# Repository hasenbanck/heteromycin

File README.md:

# Heteromycin - 3D printer board

Heteromycin is a 3D printer controller that aims to provide a full stack user
experience around Octoprint / Marlin using a custom designed board that
integrates a Raspberry Pi 3 or Zero W. It will also provide a solid, powerfull
hardware by utilizing quality components, a STM32 32bit MCU and powerfull
TMC5160 or TMC2160 driver (SD / SPI mode).

## Features

* 32bit STM32H743VI 400Mhz / 1024KiB RAM / 2MiB Flash MCU / 4 KiB EEPROM
* Integrated Raspberry Pi 3 / Zero W HAT connector as the main user interface
* Integrated DC/DC switching module for 5V / 3.3V power supply
* 5x TMC5160 or TMC2160 stepper driver with 8x external Power MOSFET each
* 3x high power MOSFET for heating (2x heater, 1x heatbed, 24V)
* 4x low power MOSFET for fans (5V or 24V)
* 40 pin external connector for STM32 and Pi GPIO pins
  * GPIO
  * PWM
  * UART
  * SPI
  * I2C
  * 3.3V / 5V / GND for external power consumption
* Micro SD Card for storing GCODE files (directa MCU access)
* Designed for a 24V power supply
* Automotive fuses
* Quality connectors
* Octoprint plugin for flashing the firmware of the board (STM32)

## Roadmap

* Hardware
  * [x] Describe the general functionality and select the main components
  * [x] Draw the schematics of the PCB
  * [x] Placement & routing of the PCB
  * [ ] Production of a development board
  * [ ] Testing the PCB
  * [ ] Repreat until hardware is finished
* Software
  * [x] Write arduino core board definition once first PCB design is finished
  * [ ] Write PIN file for Marlin
  * [ ] Test board (esp. the TMC*160 driver)
  * [ ] Octoprint plugin for firmware upgrade
  * [ ] STM32flash rewrite (fix I2C and add SPI, maybe rewrite in rust)
  * [ ] Create a script / image with Octoprint with the plugin / tools
  preinstalled
  * [ ] Documentation

## Alternative Parts

### Stepper driver

You can use both TMC5160 or TMC2160 as the stepper driver, since they both are
functionally / pin equal when used in SD / SPI-Mode.

It doesn't mater choosing one over the other, other than price and availability.

Fine tuning of the MOSFET driver may be necessary.

## License

The hardware is licensed under CERN OHL version 1.2.
The software is licensed under GNU GPL v3.

The files under PCB/packages3d are excluded from this license and are provided
under fair use terms for this open-source project.

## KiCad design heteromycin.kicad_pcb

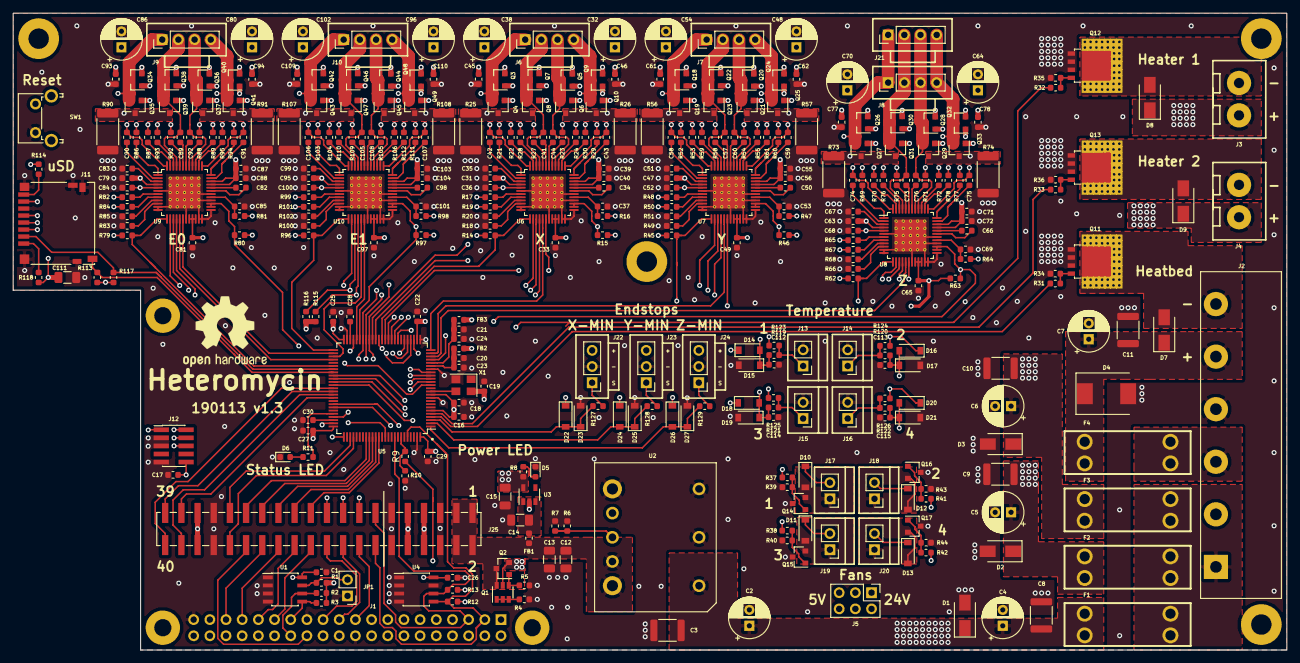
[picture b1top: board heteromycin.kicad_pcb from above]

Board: 4 copper layers, 200.0 x 100.0 mm, 373 parts (1 on the bottom side), 293 nets.

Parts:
C1, C16, C17, C18, C19, C22, C23, C24, C25, C26, C27, C29, C31, C33, C39, C40, C47, C49, C55, C56, C63, C65, C71, C72, C79, C81, C87, C88, C95, C97, C103, C104, C112, C113, C114, C115: 100nF; C_0603_1608Metric
C2, C4, C5, C6, C7, C32, C38, C48, C54, C64, C70, C80, C86, C96, C102: 100uF; CP_Radial_D6.3mm_P2.50mm
C3, C8, C9, C10, C11: 100nF; C_1812_4532Metric
C12, C14: 22uF; C_1206_3216Metric
C13: 100nF; C_1206_3216Metric
C15, C111: 10uF; C_1206_3216Metric
C20, C21: 1uF; C_0603_1608Metric
C28, C30, C35, C36, C51, C52, C67, C68, C83, C84, C99, C100: 2.2uF; C_0603_1608Metric
C34, C50, C66, C82, C98: 22nF; C_0603_1608Metric
C37, C45, C46, C53, C61, C62, C69, C77, C78, C85, C93, C94, C101, C109, C110: 470nF; C_0603_1608Metric
C41, C42, C43, C44, C57, C58, C59, C60, C73, C74, C75, C76, C89, C90, C91, C92, C105, C106, C107, C108: 220nF; C_0603_1608Metric
D1, D2, D3: SMAJ28A; D_SMA
D4: S3A-13-F; D_SMC
D5: LTST-C194KGKT; LED_0603_1608Metric
D6: LTST-C194KSKT; LED_0603_1608Metric
D7, D8, D9: SK310A-LTP; D_SMA
D10, D11, D12, D13, D14, D15, D16, D17, D18, D19, D20, D21, D22, D23, D24, D25, D26, D27: BAT54GWJ; D_SOD-123
F1, F2, F3, F4: 3557-2; KEYSTONE-FUSE-3557-2
FB1, FB2, FB3: MPZ1608S221A; R_0603_1608Metric
H1, H2, H5: MountingHole_2.7mm_M2.5_Pad
H3, H4, H6, H7: MountingHole_3.2mm_M3_Pad
J1: M20-7832046; PinSocket_2x20_P2.54mm_Vertical
J2: 4DB-P108-06
J3, J4: 39531-1002
J5: Conn_02x03_Counter_Clockwise; PinHeader_2x03_P2.54mm_Vertical
J6, J7, J8, J9, J10, J21: 70543-0003
J11: DM3D-SF; microSD_HC_Hirose_DM3D-SF
J12: 20021121-00010C4LF; PinHeader_2x05_P1.27mm_Vertical_SMD
J13, J14, J15, J16, J17, J18, J19, J20: 70543-0001
J22, J23, J24: 70543-0002
J25: Conn_02x20_Odd_Even; PinHeader_2x20_P2.54mm_Vertical_SMD
JP1: Jumper_2_Open; PinHeader_1x02_P2.54mm_Vertical
LOGO1: Logo_Open_Hardware_Large; OSHW-Logo2_14.6x12mm_SilkScreen
Q1: DMMT5401; SOT-23-6
Q2: DMG2305UX; SOT-23
Q3, Q4, Q5, Q6, Q7, Q8, Q9, Q10, Q14, Q15, Q16, Q17, Q18, Q19, Q20, Q21, Q22, Q23, Q24, Q25, Q26, Q27, Q28, Q29, Q30, Q31, Q32, Q33, Q34, Q35, Q36, Q37, Q38, Q39, Q40, Q41, Q42, Q43, Q44, Q45, Q46, Q47, Q48, Q49: IRLML0030TRPbF; SOT-23
Q11, Q12, Q13: PSMN1R2-30YLC,115; SOT-669_LFPAK_ThermalVias-1
R1, R5, R14, R15, R45, R46, R62, R63, R79, R80, R96, R97, R113, R114, R115, R116, R117, R118: 47k; R_0603_1608Metric
R2, R3: 3.9K; R_0603_1608Metric
R4, R9: 10k; R_0603_1608Metric
R6: 20k; R_0603_1608Metric
R7: 15k; R_0603_1608Metric
R8, R11, R127, R128, R129: 1k; R_0603_1608Metric
R10, R34, R35, R36, R39, R40, R43, R44: 100k; R_0603_1608Metric
R12, R13, R119, R120, R121, R122, R123, R124, R125, R126: 4.7k; R_0603_1608Metric
R16, R47, R64, R81, R98: 2.2; R_0603_1608Metric
R17, R18, R19, R20, R48, R49, R50, R51, R65, R66, R67, R68, R82, R83, R84, R85, R99, R100, R101, R102: 47; R_0603_1608Metric
R21, R22, R23, R24, R27, R28, R29, R30, R52, R53, R54, R55, R58, R59, R60, R61, R69, R70, R71, R72, R75, R76, R77, R78, R86, R87, R88, R89, R92, R93, R94, R95, R103, R104, R105, R106, R109, R110, R111, R112: 10; R_0603_1608Metric
R25, R26, R56, R57, R73, R74, R90, R91, R107, R108: 0.1; R_2512_6332Metric
R31, R32, R33, R37, R38, R41, R42: 100; R_0603_1608Metric
SW1: PTS645VL39-2; SW_Tactile_SPST_Angled_PTS645Vx39-2LFS
U1, U4: CAT24C32; SOIC-8_3.9x4.9mm_P1.27mm
U2: i3A
U3: AP7365-33WG-7; SOT-23-5
U5: STM32H743VI; TQFP-100_14x14mm_P0.5mm
U6, U7, U8, U9, U10: TMC2160-TA; TQFP-48-1EP_7x7mm_P0.5mm_EP5x5mm_ThermalVias
X1: ECS-TXO-3225-250-TR; ECS-TXO-3225

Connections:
/Connectors/MCU_MISO: J11.7, J25.17, R115.1, U5.43, U6.16, U7.16, U8.16, U9.16, U10.16
/Connectors/MCU_MOSI: J11.3, J25.19, R116.1, U5.44, U6.15, U7.15, U8.15, U9.15, U10.15
/Connectors/MCU_SCK: J11.5, J25.15, U5.42, U6.14, U7.14, U8.14, U9.14, U10.14
/Connectors/PI_SCK: J1.23, J25.20, U5.29
/Connectors/PI_SS1: J1.26, J25.30
/Connectors/PWM_EXT1: J25.37, U5.66
/Connectors/PWM_EXT2: J25.38, U5.65
/Connectors/PWM_EXT3: J25.39, U5.64
/Connectors/PWM_EXT4: J25.40, U5.63
/Connectors/RX: J25.32, U5.79
/Connectors/SCL: J1.5, J25.13, R13.1, U4.6, U5.92
/Connectors/SDA: J1.3, J25.14, R12.1, U4.5, U5.96
/Connectors/SWCLK: J12.4, U5.76
/Connectors/SWDIO: J12.2, U5.72
/Connectors/SWO: J12.6, U5.89
/Connectors/TEMP1: C112.1, D14.2, D15.1, R119.2, U5.18
/Connectors/TEMP2: C113.1, D16.2, D17.1, R120.2, U5.17
/Connectors/TEMP3: C114.1, D18.2, D19.1, R121.2, U5.16
/Connectors/TEMP4: C115.1, D20.2, D21.1, R122.2, U5.15
/Connectors/TX: J25.31, U5.78
/Connectors/X_MIN: D22.2, D23.1, R127.2, U5.3
/Connectors/Y_MIN: D24.2, D25.1, R128.2, U5.2
/Connectors/Z_MIN: D26.2, D27.1, R129.2, U5.1
/Connectors/nRESET: C17.2, J1.12, J12.10, SW1.2, U5.14
/MCU/BOOT: J1.7, R9.1
/MCU/BOOTpin: R9.2, R10.2, U5.94
/MCU/CLK: U5.12, X1.3
/MCU/D1: J25.21, U5.87
/MCU/D2: J25.23, U5.86
/MCU/D3: J25.25, U5.85
/MCU/D4: J25.27, U5.84
/MCU/D5: J25.29, U5.83
/MCU/MCU_SS: J1.24, U5.28
/MCU/PWM_BED: R31.2, U5.4
/MCU/PWM_FAN1: R37.2, U5.59
/MCU/PWM_FAN2: R41.2, U5.60
/MCU/PWM_FAN3: R38.2, U5.61
/MCU/PWM_FAN4: R42.2, U5.62
/MCU/PWM_HEAT1: R32.2, U5.22
/MCU/PWM_HEAT2: R33.2, U5.5
/MCU/SD_DETECT: J11.10, R113.1, U5.58
/MCU/STATUS_LED: R11.1, U5.71
/MCU/VCAP1: C28.2, U5.48
/MCU/VCAP2: C30.2, U5.73
/MCU/VDDA: C21.1, C24.1, FB3.1, U5.21
/MCU/VREF+: C20.2, C23.2, FB2.1, U5.20
/Raspberry Pi Connector/D1: J1.29, J25.22
/Raspberry Pi Connector/D2: J1.31, J25.24
/Raspberry Pi Connector/D3: J1.33, J25.26
/Raspberry Pi Connector/D4: J1.35, J25.28
/Raspberry Pi Connector/ID_SC_EEPROM: J1.28, R2.2, U1.6
/Raspberry Pi Connector/ID_SD_EEPROM: J1.27, R3.2, U1.5
/Raspberry Pi Connector/MISO: J1.21, J25.18, U5.30
/Raspberry Pi Connector/MOSI: J1.19, J25.16, U5.31
/Raspberry Pi Connector/RX: J1.10, U5.68
/Raspberry Pi Connector/TX: J1.8, U5.69
/Raspberry Pi Connector/VDD5V_HAT: J1.2, J1.4, Q1.5, Q2.2
/SD Card Reader/SS: J11.2, R117.1, U5.57
/Steper Motor Y/5VOUT: C52.1, R47.2, U7.5
/Steper Motor Y/12VOUT: C51.1, U7.3
/Steper Motor Y/BMA1: C60.2, J7.3, Q20.3, Q21.2, U7.40
/Steper Motor Y/BMA2: C59.2, J7.4, Q24.3, Q25.2, U7.37
/Steper Motor Y/BMB1: C58.2, J7.1, Q18.3, Q19.2, U7.48
/Steper Motor Y/BMB2: C57.2, J7.2, Q22.3, Q23.2, U7.45
/Steper Motor Y/CA1: C60.1, U7.42
/Steper Motor Y/CA2: C59.1, U7.35
/Steper Motor Y/CB1: C58.1, U7.2
/Steper Motor Y/CB2: C57.1, U7.43
/Steper Motor Y/CPI: C50.1, U7.32
/Steper Motor Y/CPO: C50.2, U7.31
/Steper Motor Y/DIAG: R46.1, U5.40, U7.26, U7.27
/Steper Motor Y/DIR: U5.35, U7.18
/Steper Motor Y/HA1: R54.1, U7.41
/Steper Motor Y/HA2: R60.2, U7.36
/Steper Motor Y/HB1: R52.1, U7.1
/Steper Motor Y/HB2: R58.2, U7.44
/Steper Motor Y/LA1: R55.1, U7.39
/Steper Motor Y/LA2: R61.2, U7.38
/Steper Motor Y/LB1: R53.1, U7.47
/Steper Motor Y/LB2: R59.2, U7.46
/Steper Motor Y/SRAH: R50.1, U7.8
/Steper Motor Y/SRAL: R51.1, U7.9
/Steper Motor Y/SRBH: R48.2, U7.7
/Steper Motor Y/SRBL: R49.1, U7.10
/Steper Motor Y/SS: R45.1, U5.36, U7.13
/Steper Motor Y/STEP: U5.24, U7.17
/Steper Motor Y/VCC: C53.1, R47.1, U7.29
/Stepper Motor E0/5VOUT: C84.1, R81.2, U9.5
/Stepper Motor E0/12VOUT: C83.1, U9.3
/Stepper Motor E0/BMA1: C92.2, J9.3, Q36.3, Q37.2, U9.40
/Stepper Motor E0/BMA2: C91.2, J9.4, Q40.3, Q41.2, U9.37
/Stepper Motor E0/BMB1: C90.2, J9.1, Q34.3, Q35.2, U9.48
/Stepper Motor E0/BMB2: C89.2, J9.2, Q38.3, Q39.2, U9.45
/Stepper Motor E0/CA1: C92.1, U9.42
/Stepper Motor E0/CA2: C91.1, U9.35
/Stepper Motor E0/CB1: C90.1, U9.2
/Stepper Motor E0/CB2: C89.1, U9.43
/Stepper Motor E0/CPI: C82.1, U9.32
/Stepper Motor E0/CPO: C82.2, U9.31
/Stepper Motor E0/DIAG: R80.1, U5.47, U9.26, U9.27
/Stepper Motor E0/DIR: U5.52, U9.18
/Stepper Motor E0/HA1: R88.1, U9.41
/Stepper Motor E0/HA2: R94.2, U9.36
/Stepper Motor E0/HB1: R86.1, U9.1
/Stepper Motor E0/HB2: R92.2, U9.44
/Stepper Motor E0/LA1: R89.1, U9.39
/Stepper Motor E0/LA2: R95.2, U9.38
/Stepper Motor E0/LB1: R87.1, U9.47
/Stepper Motor E0/LB2: R93.2, U9.46
/Stepper Motor E0/SRAH: R84.1, U9.8
/Stepper Motor E0/SRAL: R85.1, U9.9
/Stepper Motor E0/SRBH: R82.2, U9.7
/Stepper Motor E0/SRBL: R83.1, U9.10
/Stepper Motor E0/SS: R79.1, U5.56, U9.13
/Stepper Motor E0/STEP: U5.54, U9.17
/Stepper Motor E0/VCC: C85.1, R81.1, U9.29
/Stepper Motor E1/5VOUT: C100.1, R98.2, U10.5
/Stepper Motor E1/12VOUT: C99.1, U10.3
/Stepper Motor E1/BMA1: C108.2, J10.3, Q44.3, Q45.2, U10.40
/Stepper Motor E1/BMA2: C107.2, J10.4, Q48.3, Q49.2, U10.37
/Stepper Motor E1/BMB1: C106.2, J10.1, Q42.3, Q43.2, U10.48
/Stepper Motor E1/BMB2: C105.2, J10.2, Q46.3, Q47.2, U10.45
/Stepper Motor E1/CA1: C108.1, U10.42
/Stepper Motor E1/CA2: C107.1, U10.35
/Stepper Motor E1/CB1: C106.1, U10.2
/Stepper Motor E1/CB2: C105.1, U10.43
/Stepper Motor E1/CPI: C98.1, U10.32
/Stepper Motor E1/CPO: C98.2, U10.31
/Stepper Motor E1/DIAG: R97.1, U5.45, U10.26, U10.27
/Stepper Motor E1/DIR: U5.46, U10.18
/Stepper Motor E1/HA1: R105.1, U10.41
/Stepper Motor E1/HA2: R111.2, U10.36
/Stepper Motor E1/HB1: R103.1, U10.1
/Stepper Motor E1/HB2: R109.2, U10.44
/Stepper Motor E1/LA1: R106.1, U10.39
/Stepper Motor E1/LA2: R112.2, U10.38
/Stepper Motor E1/LB1: R104.1, U10.47
/Stepper Motor E1/LB2: R110.2, U10.46
/Stepper Motor E1/SRAH: R101.1, U10.8
/Stepper Motor E1/SRAL: R102.1, U10.9
/Stepper Motor E1/SRBH: R99.2, U10.7
/Stepper Motor E1/SRBL: R100.1, U10.10
/Stepper Motor E1/SS: R96.1, U5.51, U10.13
/Stepper Motor E1/STEP: U5.53, U10.17
/Stepper Motor E1/VCC: C101.1, R98.1, U10.29
/Stepper Motor X/5VOUT: C36.1, R16.2, U6.5
/Stepper Motor X/12VOUT: C35.1, U6.3
/Stepper Motor X/BMA1: C44.2, J6.3, Q5.3, Q6.2, U6.40
/Stepper Motor X/BMA2: C43.2, J6.4, Q9.3, Q10.2, U6.37
/Stepper Motor X/BMB1: C42.2, J6.1, Q3.3, Q4.2, U6.48
/Stepper Motor X/BMB2: C41.2, J6.2, Q7.3, Q8.2, U6.45
/Stepper Motor X/CA1: C44.1, U6.42
/Stepper Motor X/CA2: C43.1, U6.35
/Stepper Motor X/CB1: C42.1, U6.2
/Stepper Motor X/CB2: C41.1, U6.43
/Stepper Motor X/CPI: C34.1, U6.32
/Stepper Motor X/CPO: C34.2, U6.31
/Stepper Motor X/DIAG: R15.1, U5.41, U6.26, U6.27
/Stepper Motor X/DIR: U5.37, U6.18
/Stepper Motor X/HA1: R23.1, U6.41
/Stepper Motor X/HA2: R29.2, U6.36
/Stepper Motor X/HB1: R21.1, U6.1
/Stepper Motor X/HB2: R27.2, U6.44
/Stepper Motor X/LA1: R24.1, U6.39
/Stepper Motor X/LA2: R30.2, U6.38
/Stepper Motor X/LB1: R22.1, U6.47
/Stepper Motor X/LB2: R28.2, U6.46
/Stepper Motor X/SRAH: R19.1, U6.8
/Stepper Motor X/SRAL: R20.1, U6.9
/Stepper Motor X/SRBH: R17.2, U6.7
/Stepper Motor X/SRBL: R18.1, U6.10
/Stepper Motor X/SS: R14.1, U5.38, U6.13
/Stepper Motor X/STEP: U5.25, U6.17
/Stepper Motor X/VCC: C37.1, R16.1, U6.29
/Stepper Motor Z/5VOUT: C68.1, R64.2, U8.5
/Stepper Motor Z/12VOUT: C67.1, U8.3
/Stepper Motor Z/BMA1: C76.2, J8.3, J21.3, Q28.3, Q29.2, U8.40
/Stepper Motor Z/BMA2: C75.2, J8.4, J21.4, Q32.3, Q33.2, U8.37
/Stepper Motor Z/BMB1: C74.2, J8.1, J21.1, Q26.3, Q27.2, U8.48
/Stepper Motor Z/BMB2: C73.2, J8.2, J21.2, Q30.3, Q31.2, U8.45
/Stepper Motor Z/CA1: C76.1, U8.42
/Stepper Motor Z/CA2: C75.1, U8.35
/Stepper Motor Z/CB1: C74.1, U8.2
/Stepper Motor Z/CB2: C73.1, U8.43
/Stepper Motor Z/CPI: C66.1, U8.32
/Stepper Motor Z/CPO: C66.2, U8.31
/Stepper Motor Z/DIAG: R63.1, U5.39, U8.26, U8.27
/Stepper Motor Z/DIR: U5.33, U8.18
/Stepper Motor Z/HA1: R71.1, U8.41
/Stepper Motor Z/HA2: R77.2, U8.36
/Stepper Motor Z/HB1: R69.1, U8.1
/Stepper Motor Z/HB2: R75.2, U8.44
/Stepper Motor Z/LA1: R72.1, U8.39
/Stepper Motor Z/LA2: R78.2, U8.38
/Stepper Motor Z/LB1: R70.1, U8.47
/Stepper Motor Z/LB2: R76.2, U8.46
/Stepper Motor Z/SRAH: R67.1, U8.8
/Stepper Motor Z/SRAL: R68.1, U8.9
/Stepper Motor Z/SRBH: R65.2, U8.7
/Stepper Motor Z/SRBL: R66.1, U8.10
/Stepper Motor Z/SS: R62.1, U5.34, U8.13
/Stepper Motor Z/STEP: U5.23, U8.17
/Stepper Motor Z/VCC: C69.1, R64.1, U8.29
BED_OUT: D7.2, J2.6, Q11.5
FAN1_OUT: D10.2, J17.1, Q14.2
FAN2_OUT: D12.2, J18.1, Q16.2
FAN3_OUT: D11.2, J19.1, Q15.2
FAN4_OUT: D13.2, J20.1, Q17.2
GND: C1.2, C2.2, C3.2, C4.2, C5.2, C6.2, C7.2, C8.2, C9.2, C10.2, C11.2, C12.2, C13.2, C14.2, C15.2, C16.2, C17.1, C18.2, C19.2, C20.1, C21.2, C22.2, C23.1, C24.2, C25.2, C26.2, C27.2, C28.1, C29.2, C30.1, C31.2, C32.2, C33.2, C35.2, C36.2, C37.2, C38.2, C39.2, C40.2, C45.2, C46.2, C47.2, C48.2, C49.2, C51.2, C52.2, C53.2, C54.2, C55.2, C56.2, C61.2, C62.2, C63.2, C64.2, C65.2, C67.2, C68.2, C69.2, C70.2, C71.2, C72.2, C77.2, C78.2, C79.2, C80.2, C81.2, C83.2, C84.2, C85.2, C86.2, C87.2, C88.2, C93.2, C94.2, C95.2, C96.2, C97.2, C99.2, C100.2, C101.2, C102.2, C103.2, C104.2, C109.2, C110.2, C111.2, C112.2, C113.2, C114.2, C115.2, D1.2, D2.2, D3.2, D4.2, D5.1, D6.1, D15.2, D17.2, D19.2, D21.2, D23.2, D25.2, D27.2, J1.6, J1.9, J1.14, J1.20, J1.25, J1.30, J1.34, J1.39, J2.2, J2.4, J11.6, J11.9, J11.11, J12.3, J12.5, J12.9, J13.2, J14.2, J15.2, J16.2, J22.2, J23.2, J24.2, J25.5, J25.6, J25.11, J25.12, J25.33, J25.34, JP1.1, Q11.1, Q11.2, Q11.3, Q12.1, Q12.2, Q12.3, Q13.1, Q13.2, Q13.3, Q14.3, Q15.3, Q16.3, Q17.3, R4.2, R5.2, R6.2, R7.2, R10.1, R18.2, R20.2, R25.1, R26.1, R34.1, R35.1, R36.1, R39.1, R40.1, R43.1, R44.1, R49.2, R51.2, R56.1, R57.1, R66.2, R68.2, R73.1, R74.1, R83.2, R85.2, R90.1, R91.1, R100.2, R102.2, R107.1, R108.1, SW1.1, U1.1, U1.2, U1.3, U1.4, U2.2, U2.3, U2.4, U3.2, U4.1, U4.2, U4.3, U4.4, U4.7, U5.10, U5.19, U5.26, U5.49, U5.74, U5.99, U6.6, U6.11, U6.12, U6.19, U6.23, U6.24, U6.25, U6.28, U6.30, U6.49, U7.6, U7.11, U7.12, U7.19, U7.23, U7.24, U7.25, U7.28, U7.30, U7.49, U8.6, U8.11, U8.12, U8.19, U8.23, U8.24, U8.25, U8.28, U8.30, U8.49, U9.6, U9.11, U9.12, U9.19, U9.23, U9.24, U9.25, U9.28, U9.30, U9.49, U10.6, U10.11, U10.12, U10.19, U10.23, U10.24, U10.25, U10.28, U10.30, U10.49, X1.2
HEAT1_OUT: D8.2, J3.1, Q12.5
HEAT2_OUT: D9.2, J4.1, Q13.5
unnamed: C14.1, FB1.1, U3.1, U3.3
unnamed: D5.2, R8.2
unnamed: D6.2, R11.2
unnamed: F1.2, F2.2, F3.2, J2.1
unnamed: F4.2, J2.3
unnamed: J11.1, R118.1
unnamed: J11.8, R114.1
unnamed: J13.1, R119.1, R123.2
unnamed: J14.1, R120.1, R124.2
unnamed: J15.1, R121.1, R125.2
unnamed: J16.1, R122.1, R126.2
unnamed: J22.1, R127.1
unnamed: J23.1, R128.1
unnamed: J24.1, R129.1
unnamed: JP1.2, R1.1, U1.7
unnamed: Q1.1, Q1.2, Q1.3, R4.1
unnamed: Q1.4, Q2.1, R5.1
unnamed: Q3.1, R21.2
unnamed: Q4.1, R22.2
unnamed: Q4.3, Q8.3, R17.1, R25.2
unnamed: Q5.1, R23.2
unnamed: Q6.1, R24.2
unnamed: Q7.1, R27.1
unnamed: Q8.1, R28.1
unnamed: Q9.1, R29.1
unnamed: Q10.1, R30.1
unnamed: Q6.3, Q10.3, R19.2, R26.2
unnamed: Q11.4, R31.1, R34.2
unnamed: Q12.4, R32.1, R35.2
unnamed: Q13.4, R33.1, R36.2
unnamed: Q14.1, R37.1, R39.2
unnamed: Q15.1, R38.1, R40.2
unnamed: Q16.1, R41.1, R43.2
unnamed: Q17.1, R42.1, R44.2
unnamed: Q18.1, R52.2
unnamed: Q19.1, R53.2
unnamed: Q19.3, Q23.3, R48.1, R56.2
unnamed: Q20.1, R54.2
unnamed: Q21.1, R55.2
unnamed: Q21.3, Q25.3, R50.2, R57.2
unnamed: Q22.1, R58.1
unnamed: Q23.1, R59.1
unnamed: Q24.1, R60.1
unnamed: Q25.1, R61.1
unnamed: Q26.1, R69.2
unnamed: Q27.1, R70.2
unnamed: Q27.3, Q31.3, R65.1, R73.2
unnamed: Q28.1, R71.2
unnamed: Q29.1, R72.2
unnamed: Q29.3, Q33.3, R67.2, R74.2
unnamed: Q30.1, R75.1
unnamed: Q31.1, R76.1
unnamed: Q32.1, R77.1
unnamed: Q33.1, R78.1
unnamed: Q34.1, R86.2
unnamed: Q35.1, R87.2
unnamed: Q35.3, Q39.3, R82.1, R90.2
unnamed: Q36.1, R88.2
unnamed: Q37.1, R89.2
unnamed: Q37.3, Q41.3, R84.2, R91.2
unnamed: Q38.1, R92.1
unnamed: Q39.1, R93.1
unnamed: Q40.1, R94.1
unnamed: Q41.1, R95.1
unnamed: Q42.1, R103.2
unnamed: Q43.1, R104.2
unnamed: Q43.3, Q47.3, R99.1, R107.2
unnamed: Q44.1, R105.2
unnamed: Q45.1, R106.2
unnamed: Q45.3, Q49.3, R101.2, R108.2
unnamed: Q46.1, R109.1
unnamed: Q47.1, R110.1
unnamed: Q48.1, R111.1
unnamed: Q49.1, R112.1
unnamed: R6.1, R7.1, U2.6
VDD3V3: C1.1, C15.1, C16.1, C18.1, C19.1, C22.1, C25.1, C26.1, C27.1, C29.1, C33.1, C49.1, C65.1, C81.1, C97.1, C111.1, D14.1, D16.1, D18.1, D20.1, D22.1, D24.1, D26.1, FB2.2, FB3.2, J11.4, J12.1, J22.3, J23.3, J24.3, J25.7, J25.8, J25.9, J25.10, J25.35, J25.36, R1.2, R2.1, R3.1, R8.1, R12.2, R13.2, R14.2, R15.2, R45.2, R46.2, R62.2, R63.2, R79.2, R80.2, R96.2, R97.2, R113.2, R114.2, R115.2, R116.2, R117.2, R118.2, R123.1, R124.1, R125.1, R126.1, U1.8, U3.5, U4.8, U5.6, U5.11, U5.27, U5.50, U5.75, U5.100, U6.20, U6.21, U6.22, U7.20, U7.21, U7.22, U8.20, U8.21, U8.22, U9.20, U9.21, U9.22, U10.20, U10.21, U10.22, X1.4
VDD5V: C12.1, C13.1, FB1.2, J5.5, J5.6, J25.1, J25.2, J25.3, J25.4, Q1.6, Q2.3, U2.7, U2.8
VDD24V: C2.1, C3.1, C4.1, C8.1, C31.1, C32.1, C38.1, C39.1, C40.1, C45.1, C46.1, C47.1, C48.1, C54.1, C55.1, C56.1, C61.1, C62.1, C63.1, C64.1, C70.1, C71.1, C72.1, C77.1, C78.1, C79.1, C80.1, C86.1, C87.1, C88.1, C93.1, C94.1, C95.1, C96.1, C102.1, C103.1, C104.1, C109.1, C110.1, D1.1, F1.1, J5.1, J5.2, Q3.2, Q5.2, Q7.2, Q9.2, Q18.2, Q20.2, Q22.2, Q24.2, Q26.2, Q28.2, Q30.2, Q32.2, Q34.2, Q36.2, Q38.2, Q40.2, Q42.2, Q44.2, Q46.2, Q48.2, U2.1, U6.4, U6.33, U6.34, U7.4, U7.33, U7.34, U8.4, U8.33, U8.34, U9.4, U9.33, U9.34, U10.4, U10.33, U10.34
VDD_BED: C7.1, C11.1, D4.1, D7.1, F4.1, J2.5
VDD_FAN: D10.1, D11.1, D12.1, D13.1, J5.3, J5.4, J17.2, J18.2, J19.2, J20.2
VDD_HEAT1: C5.1, C9.1, D2.1, D8.1, F2.1, J3.2
VDD_HEAT2: C6.1, C10.1, D3.1, D9.1, F3.1, J4.2

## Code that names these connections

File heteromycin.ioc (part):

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Mcu.Name=STM32H743VITx
Mcu.Package=LQFP100
Mcu.UserName=STM32H743VITx
PA0.GPIOParameters=GPIO_Label
PA0.GPIO_Label=PWM_HEAT1
PA0.Signal=S_TIM2_CH1
PA1.GPIOParameters=GPIO_Label
PA1.GPIO_Label=STEP_Z
PA1.Signal=S_TIM2_CH2
PA10.Mode=Asynchronous
PA10.Signal=USART1_RX
PA12.GPIOParameters=GPIO_Label
PA12.GPIO_Label=STATUS_LED
PA12.Signal=GPIO_Output
PA13\ (JTMS/SWDIO).Mode=Trace_Asynchronous_SW
PA13\ (JTMS/SWDIO).Signal=SYS_JTMS-SWDIO
PA14\ (JTCK/SWCLK).Mode=Trace_Asynchronous_SW
PA14\ (JTCK/SWCLK).Signal=SYS_JTCK-SWCLK
PA2.GPIOParameters=GPIO_Label
PA2.GPIO_Label=STEP_Y
PA2.Signal=S_TIM2_CH3
PA3.GPIOParameters=GPIO_Label
PA3.GPIO_Label=STEP_X
PA3.Signal=S_TIM2_CH4
PA4.GPIOParameters=GPIO_Label
PA4.GPIO_Label=MCU_SS
PA4.Mode=NSS_Signal_Hard_Input
PA4.Signal=SPI1_NSS
PA5.Mode=Full_Duplex_Master
PA5.Signal=SPI1_SCK
PA6.Mode=Full_Duplex_Master
PA6.Signal=SPI1_MISO
PA7.Mode=Full_Duplex_Master
PA7.Signal=SPI1_MOSI
PA9.Mode=Asynchronous
PA9.Signal=USART1_TX
PB0.GPIOParameters=GPIO_Label
PB0.GPIO_Label=SS_Z
PB0.Signal=GPIO_Output
PB1.GPIOParameters=GPIO_Label
PB1.GPIO_Label=DIR_Y
PB1.Signal=GPIO_Output
PB10.GPIOParameters=GPIO_Label
PB10.GPIO_Label=DIR_E1
PB10.Signal=GPIO_Output
PB11.GPIOParameters=GPIO_Label
PB11.GPIO_Label=DIAG_E0
PB11.Signal=GPIO_Input
PB12.GPIOParameters=GPIO_Label
PB12.GPIO_Label=SS_E1
PB12.Signal=GPIO_Output
PB13.GPIOParameters=GPIO_Label
PB13.GPIO_Label=DIR_E0
PB13.Signal=GPIO_Output
PB14.GPIOParameters=GPIO_Label
PB14.GPIO_Label=STEP_E1
PB14.Signal=S_TIM12_CH1
PB15.GPIOParameters=GPIO_Label
PB15.GPIO_Label=STEP_E0
PB15.Signal=S_TIM12_CH2
PB2.GPIOParameters=GPIO_Label
PB2.GPIO_Label=SS_Y
PB2.Signal=GPIO_Output
PB3\ (JTDO/TRACESWO).Mode=Trace_Asynchronous_SW
PB3\ (JTDO/TRACESWO).Signal=SYS_JTDO-SWO
PB6.Mode=I2C
PB6.Signal=I2C1_SCL
PB9.Mode=I2C
PB9.Signal=I2C1_SDA
PC0.GPIOParameters=GPIO_Label
PC0.GPIO_Label=TEMP4
PC0.Signal=ADCx_INP10
PC1.GPIOParameters=GPIO_Label
PC1.GPIO_Label=TEMP3
PC1.Signal=ADCx_INP11
PC10.Mode=Asynchronous
PC10.Signal=USART3_TX
PC11.Mode=Asynchronous
PC11.Signal=USART3_RX
PC2_C.GPIOParameters=GPIO_Label
PC2_C.GPIO_Label=TEMP2
PC2_C.Mode=IN0-Single-Ended
PC2_C.Signal=ADC3_INP0
PC3_C.GPIOParameters=GPIO_Label
PC3_C.GPIO_Label=TEMP1
PC3_C.Mode=IN1-Single-Ended
PC3_C.Signal=ADC3_INP1
PC5.GPIOParameters=GPIO_Label
PC5.GPIO_Label=DIR_Z
PC5.Signal=GPIO_Output
PC6.GPIOParameters=GPIO_Label
PC6.GPIO_Label=PWM_EXT4
PC6.Signal=S_TIM3_CH1
PC7.GPIOParameters=GPIO_Label
PC7.GPIO_Label=PWM_EXT3
PC7.Signal=S_TIM3_CH2
PC8.GPIOParameters=GPIO_Label
PC8.GPIO_Label=PWM_EXT2
PC8.Signal=S_TIM3_CH3
PC9.GPIOParameters=GPIO_Label
PC9.GPIO_Label=PWM_EXT1
PC9.Signal=S_TIM3_CH4
PD10.GPIOParameters=GPIO_Label
PD10.GPIO_Label=SS_SD
PD10.Signal=GPIO_Output
PD11.GPIOParameters=GPIO_Label
PD11.GPIO_Label=SD_DETECT
PD11.Signal=GPIO_Input
PD12.GPIOParameters=GPIO_Label
PD12.GPIO_Label=PWM_FAN1
PD12.Signal=S_TIM4_CH1
PD13.GPIOParameters=GPIO_Label
PD13.GPIO_Label=PWM_FAN2
PD13.Signal=S_TIM4_CH2
PD14.GPIOParameters=GPIO_Label
PD14.GPIO_Label=PWM_FAN3
PD14.Signal=S_TIM4_CH3
PD15.GPIOParameters=GPIO_Label
PD15.GPIO_Label=PWM_FAN4
PD15.Signal=S_TIM4_CH4
PD2.GPIOParameters=GPIO_Label
PD2.GPIO_Label=D5
PD2.Signal=GPIO_Input
PD3.GPIOParameters=GPIO_Label
PD3.GPIO_Label=D4
PD3.Signal=GPIO_Input
PD4.GPIOParameters=GPIO_Label
PD4.GPIO_Label=D3
PD4.Signal=GPIO_Input
PD5.GPIOParameters=GPIO_Label
PD5.GPIO_Label=D2
PD5.Signal=GPIO_Input
PD6.GPIOParameters=GPIO_Label
PD6.GPIO_Label=D1
PD6.Signal=GPIO_Input
PD9.GPIOParameters=GPIO_Label
PD9.GPIO_Label=SS_E0
PD9.Signal=GPIO_Output
PE10.GPIOParameters=GPIO_Label
PE10.GPIO_Label=DIAG_Y
PE10.Signal=GPIO_Input
PE11.GPIOParameters=GPIO_Label
PE11.GPIO_Label=DIAG_X
PE11.Signal=GPIO_Input
PE12.Mode=Full_Duplex_Master
PE12.Signal=SPI4_SCK
PE13.Mode=Full_Duplex_Master
PE13.Signal=SPI4_MISO
PE14.Mode=Full_Duplex_Master
PE14.Signal=SPI4_MOSI
PE15.GPIOParameters=GPIO_Label
PE15.GPIO_Label=DIAG_E1
PE15.Signal=GPIO_Input
PE2.GPIOParameters=GPIO_Label
PE2.GPIO_Label=Z_MIN
PE2.Signal=GPIO_Input
PE3.GPIOParameters=GPIO_Label
PE3.GPIO_Label=Y_MIN
PE3.Signal=GPIO_Input
PE4.GPIOParameters=GPIO_Label
PE4.GPIO_Label=X_MIN
PE4.Signal=GPIO_Input
PE5.GPIOParameters=GPIO_Label
PE5.GPIO_Label=PWM_BED
PE5.Signal=S_TIM15_CH1
PE6.GPIOParameters=GPIO_Label
PE6.GPIO_Label=PWM_HEAT2
PE6.Signal=S_TIM15_CH2
PE7.GPIOParameters=GPIO_Label
PE7.GPIO_Label=DIR_X
PE7.Signal=GPIO_Output
PE8.GPIOParameters=GPIO_Label
PE8.GPIO_Label=SS_X
PE8.Signal=GPIO_Output
PE9.GPIOParameters=GPIO_Label
PE9.GPIO_Label=DIAG_Z
PE9.Signal=GPIO_Input
PH0-OSC_IN\ (PH0).Mode=HSE-External-Clock-Source
PH0-OSC_IN\ (PH0).Signal=RCC_OSC_IN
PH1-OSC_OUT\ (PH1).Mode=HSE-External-Clock-Source
PH1-OSC_OUT\ (PH1).Signal=RCC_OSC_OUT
RCC.SYSCLKFreq_VALUE=400000000
RCC.SYSCLKSource=RCC_SYSCLKSOURCE_PLLCLK
board=custom

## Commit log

2018-10-12 Initial commit
    Added a README and information about the licenses the project
    will use.
2018-10-14 Snapshot of current development
2018-10-16 Current snapshot
2018-10-16 Finished general layout and power planes
2018-10-17 Add SD card reader, placed temp connections, fixed stepper placement
2018-10-17 Add peripheral configuration in CubeMX configuration file
2018-10-17 Fix pin layout
2018-10-18 Placed some bypass caps
2018-10-19 Placed last connectors
2018-10-20 Some small adjustments
2018-10-20 First pass of routing
2018-10-20 Some silkscreen changes
2018-10-21 Various changes
    * Add Status LED
    * Switched small diodes to more general available BAT54 in SOD123
    * Fixed various DRC errors
2018-10-21 Add i3a component
2018-10-21 Complete functional design
2018-10-21 Finish silkscreen and updated README.md
2018-10-21 Fix spelling in README.md
2018-10-21 Fix ZVD for RPi protection
2018-10-22 Change default SOT1220 MOSFET and added parts alternatives
2018-10-23 Add drawings and another mounting hole
2018-10-23 Change mounting holes
    Pi mounting holes: M2.5
    Board mounting holes: M3
    Added a mounting hole near the board center
2018-10-23 Update image and corrected some copper pure
2018-10-23 Add RPi HAT eeprom tool
2018-10-23 Add EEPROM settings configuration
2018-10-23 Correct EEPROM settings
2018-10-24 Add bypass cap for I2C EEPROMs and redone some copper pour
2018-10-24 Fix MOSFET selection
2018-10-24 Add transistor for boot selection
2018-10-24 Move the nRESET cap a little bit
2018-10-25 Update TXCO and STM32CubeMX configuration file
2018-10-25 Correct the name of the micro SD card reader
2018-10-25 Change PI connector to a cheaper one
2018-10-26 Fix current sense resistor to correct value and add BOM
2018-10-26 Increase date code for v1.0 release
2018-10-26 Increase pin tolerance for i3A DC/DC
2018-10-27 Add discord link
2018-11-10 Fix various v1.0 errors
    * Change 3.3V LDO to AP7365-33WG-7
    * Optimize soldermask clearance (from 0.2 to 0.05)
    * Connect SD connect switch to GND
    * Optimized some PADs
2018-11-10 Add v1.1 BOM and update picture
2018-11-10 Fixed heater output cap
2018-11-20 Add thermal relief to DC/DC switcher connection
2018-11-20 Change BOM to v1.2
    02x20 connector had the wrong part number.
2018-11-20 Change version to 1.2
2018-11-24 Version 1.3
    * Changed to TH 100uF capacitators
    * Switched to SOT-23-3 MOSFETS
2018-11-24 Updated board to version 1.2
    * Switched small MOSFETs to SOT-23 package
    * Redesigned TMC*160 driver layout
    * Changed 01x03 to 02x03 jumper for FAN voltage selection
    * Switches STATUS_LED pin
    * Some copper pour optimizations
2018-11-24 Increased sense resistor value to 0.1
    This will result in a maximum 2.3A current for the stepper.
    This should act as a more sensible default. Of course the user
    can replace the sense resistors as they see fit. As long as they
    they don't stress the termal budget of the driver MOSFET that is.
2018-11-24 Add silkscreen explanation for endstop pins
2018-11-24 Connected TMC DIAG pins to MCU
    We had some pins free, so I decided to connect them, so that we
    don't need to use the ENDSTOP OVER SPI feature.
2018-11-24 Updated image and added some copper pour
2018-11-25 Updated BOM for version 1.2
2018-12-02 Switched EEPROM I2C traces for the RPI
    SDA and SCL were switched. Also some formatting for the
    EEPROM settings.txt.
2018-12-02 Add PU for SD_DETECT_PIN
2018-12-23 Update the MCU from STM32F765VI to STM32H743VI
    More speed, more RAM. Only loose the compability to flash over
    USART3. Flashing over USART1/I2C/SPI is still possible.
2019-01-11 Improve Readability
2019-01-11 Further Improved Readability - Rotated labels
2019-01-11 Re-place some items that had broken timestamps
2019-01-12 Changed boot pin drive interface
    Changed the boot pin to a direct connection since the current design depends on a existing raspberry to work. Used a 10kOhms resistor since that's the one used in the development board made by ST
2019-01-12 Add PD resistor to BOOT PIN
2019-01-12 Changed BOOT PIN PD resistor to 100kOhms
2019-01-12 Fix label position
2019-01-12 Rotated BOOT PIN resistor
2019-01-12 Designed a layout sheet file
2019-01-13 Fix BOOT PIN track
2019-01-13 Remove old note and add notice for 100V cap on motor driver
    Anothe developer is using a RC for KiCad 6, so I need to re-
    convert and touch all files with this commit. The developer
    has been lectured and this shouldn't be necessary in the future.
2019-01-13 Prepare release 1.3
    * Fix LFPAK footprint (gaps)
    * Updated BOM for release 1.3
    * Updated silkscreen version number
2019-01-13 Fixed wrong partnumber for TXCO
2019-01-13 Fix BOM for the correct 40 PIN header
2019-01-13 Added LCSC Distributor to BOM
2019-01-13 Fix part number for 100uF cap
2019-01-13 Added manufacturer number to schematic
2019-01-13 Re anotate design
2020-04-30 Remove the discord link.
